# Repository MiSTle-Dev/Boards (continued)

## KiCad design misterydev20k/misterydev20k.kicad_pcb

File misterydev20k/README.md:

# MiSTeryDev20k

This is the first complete custom board which does *not* need daughter boards
like the [Tang Nano 20k](https://wiki.sipeed.com/hardware/en/tang/tang-nano-20k/nano-20k.html) or
the [Raspberry Pi Pico](https://www.raspberrypi.com/documentation/microcontrollers/pico-series.html).

The board features the [Gowin GW2AR-LV18QN88C8/I7](https://www.gowinsemi.com/en/product/detail/38/) FPGA present on the Tang Nano 20k and runs the same cores as that device including the [NanoMig](http://github.com/MiSTle-Dev/NanoMig) and [MisteryNano](http://github.com/MiSTle-Dev/MiSTeryNano).

This board can be manfactured through [JLCPCBs assembly service](http://jlcpcb.com) using the [production data](production).

The main objective of this board is to run known-good cores and
firmware and test a few features that couldn't be implemented and
tested with the Tang Nano 20k. These include:

  - Use the RP2040 for JTAG programming of the FPGA :heavy_check_mark:
    - Using openFPGAloader :heavy_check_mark:
    - Using Gowin Graphical Programmer :heavy_check_mark:
    - Using Gowin Programmer CLI :heavy_check_mark:
    - Extensive analysis and debugging of USB/JTAG commands as they pass the rp2040 :heavy_check_mark:
  - Additional access to the SD card directly from the RP2040 :heavy_check_mark:
    - SPI access is not possible since the SD card cannot return into SD card mode for FPGA usage
    - 1-bit SD mode work via software bitbang and achieves ~700kBytes/s :heavy_check_mark:
  - Control the FPGA directly from the RP2040 :heavy_check_mark:
    - Boot the FPGA from ```.fs``` file from SD card :heavy_check_mark:
    - Boot the FPGA from ```.bin``` file from SD card :heavy_check_mark:
  - Test SPI PSRAM
  - Optionally use the RP2040's native USB via the USB Hub

Further minor improvements over the existing boards are:

  - Two DB9 joysticks :heavy_check_mark: 
  - MIDI on M5 Stack connector :heavy_check_mark:

[Schematic PDF](misterydev20k_sch.pdf)
[Layout PDF](misterydev20k_board.pdf)	

## Current state

  - Schematic :heavy_check_mark:
  - Initial PCB layout :heavy_check_mark:
  - LCSC part mapping :heavy_check_mark:
  - BOM verification :heavy_check_mark:
  - Final PCB layout :heavy_check_mark:
  - Prepare JLCPCB [production data](production) :heavy_check_mark:
  - FPGA [stock](https://jlcpcb.com/partdetail/5794058-GW2AR_LV18QN88C8I7/C9900028472) :heavy_check_mark:
  - Order placed :heavy_check_mark:
  - Order shipped :heavy_check_mark:
  - Order stuck in customs :heavy_check_mark:	
  - Boards arrived :heavy_check_mark:
  - Basic 90% function test using Atari ST core :heavy_check_mark:
  - Extensive testing :heavy_check_mark:
  - New features :heavy_check_mark:

Upated in V1.1:
  - WS2812 was powered by 3.3V, corrected to 5V
  - JLCPCB BOM contained 16MBit flash for Pico and FPGA, are now 64MBit
  - Pico debug header labels on PCB were in reverse order

## Usage

The latest FPGA Companion has the ability to load cores
from SD card. Before doing so, please make sure you have a working
setup by placing the core and the ROMs in flash and using an SD card
with matching contents. Also build and install the latest FPGA
Companion for the DEV20K board to make sure the SD card and JTAG
functionality is included.

If this works fine, then replace the core in flash by any core that
does _not_ implement the FPGA Companions SPI interface.  You might use
this [test core](./test) which will display the MiSTle logo. Then
place the retro core you are using on the SD card. You can use the
```.fs``` file, but it's download from SD card to the FPGA will take
over 10 seconds as that's a huge ASCII file. Instead you might want
use the ```.bin``` file that is also generated by the
synthesis. Alternally, the ```.bin``` can be gerated from the
```.fs``` file using the gowin programmer:

```
programmer_cli --filestransform 1 --files test.fs
```

The core needs to be renamed to ```core.fs``` or ```core.bin``` when
placed on SD card. The board will then load the test core after
powerup. After 5 seconds it will timeout waiting for the core to
communicate. It will then search for ```core.bin``` and if that
fails for ```core.fs``` on the SD card. If present the core will
be downloaded to the FPGA and the system is rebooted using the
core.

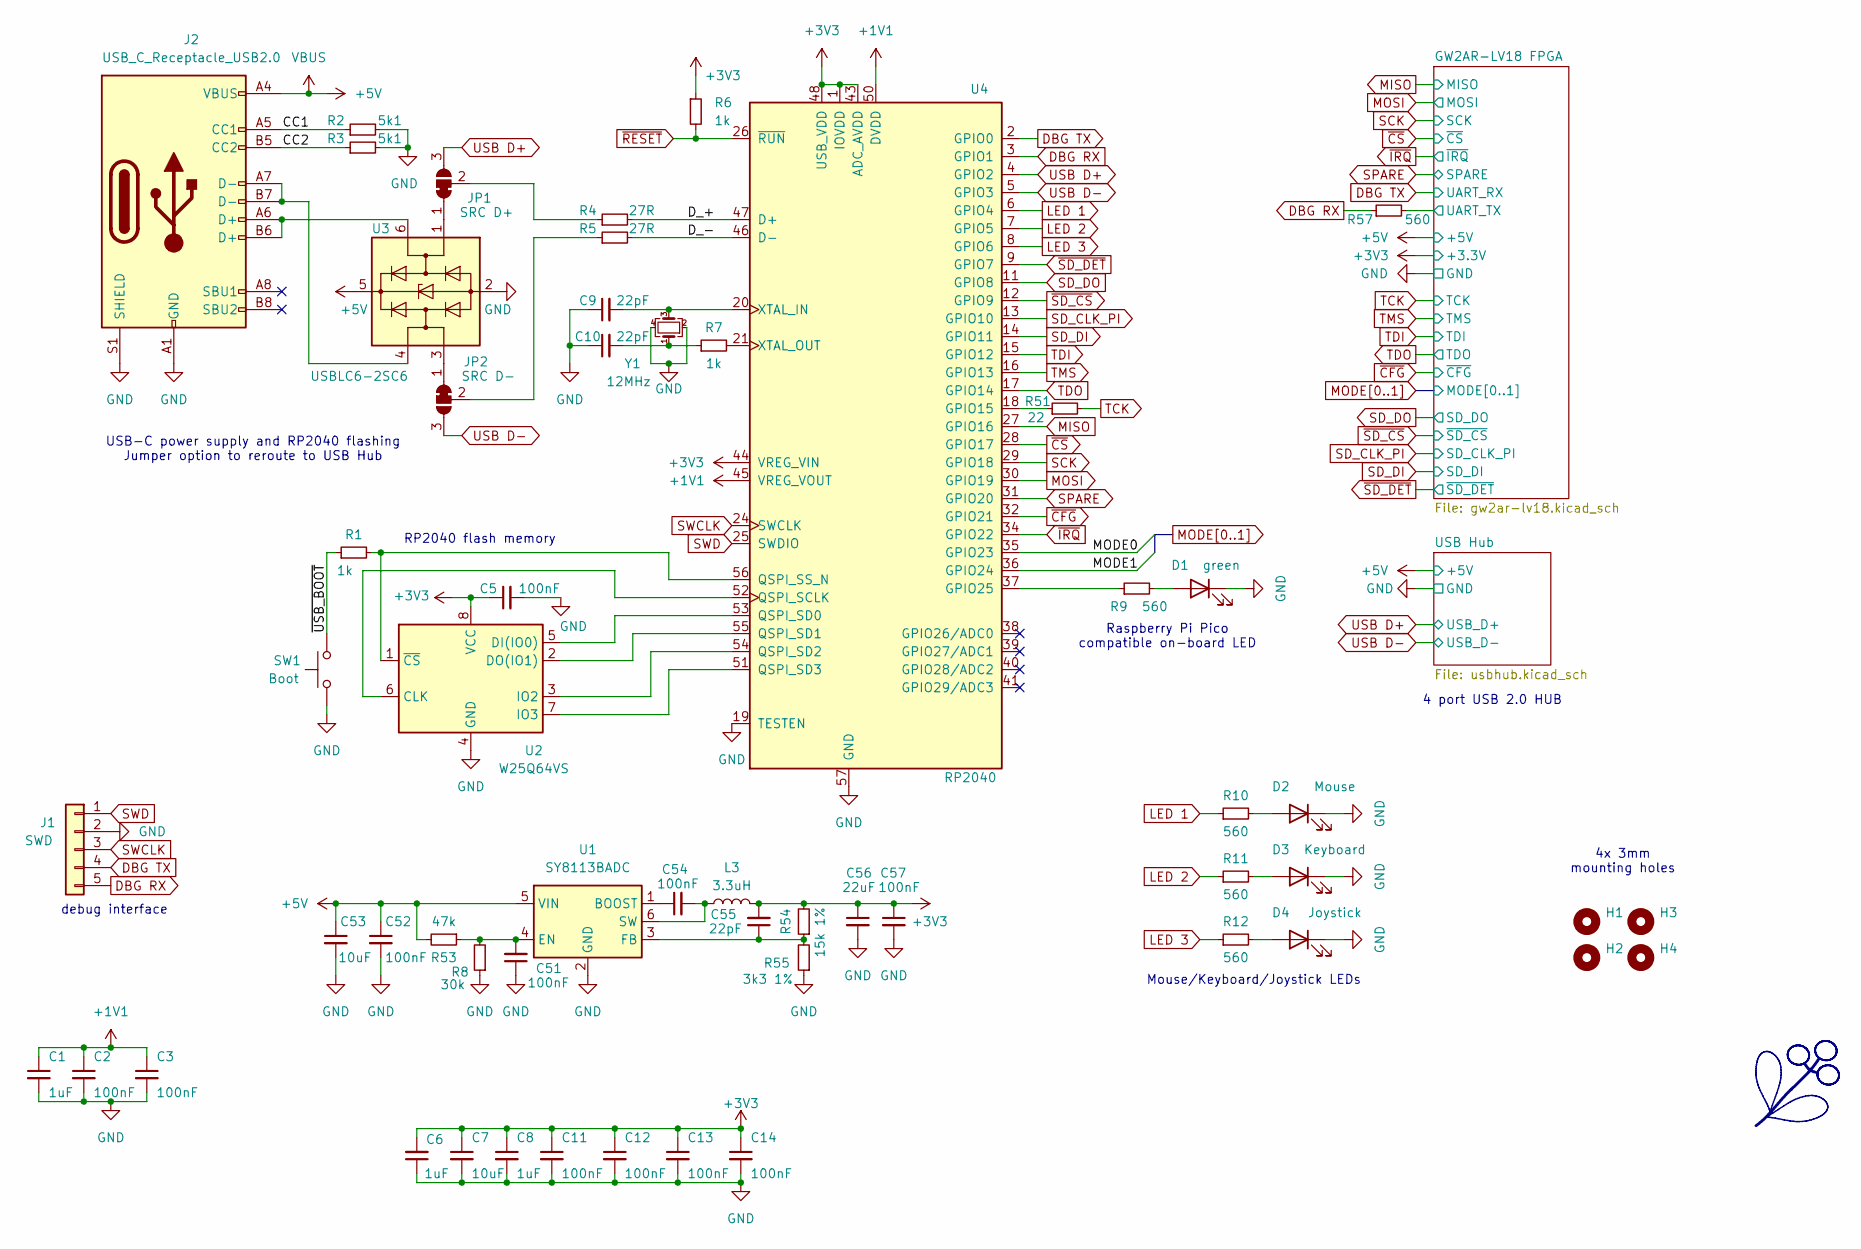
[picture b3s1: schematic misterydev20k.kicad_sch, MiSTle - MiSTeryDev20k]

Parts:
C1, C6, C8: 1uF; C_0402_1005Metric; LCSC Part # C52923
C2, C3, C5, C11, C12, C13, C14, C51, C54: 100nF; C_0402_1005Metric; LCSC Part # C1525
C7: 10uF; C_0402_1005Metric; LCSC Part # C15525
C9, C10, C55: 22pF; C_0402_1005Metric; LCSC Part # C1555
C52, C57: 100nF; C_0603_1608Metric; LCSC Part # C14663
C53: 10uF; C_0603_1608Metric; LCSC Part # C19702
C56: 22uF; C_0603_1608Metric; LCSC Part # C84419
D1: green; LED_0805_2012Metric; LCSC Part # C2297
D2: Mouse; LED_0805_2012Metric; LCSC Part # C2297
D3: Keyboard; LED_0805_2012Metric; LCSC Part # C2297
D4: Joystick; LED_0805_2012Metric; LCSC Part # C2297
H1, H2, H3, H4: MountingHole; MountingHole_3.2mm_M3
J1: SWD; PinHeader_1x05_P2.54mm_Vertical; LCSC Part # C492404
J2: USB_C_Receptacle_USB2.0; USB_C_Receptacle_HRO_TYPE-C-31-M-12; LCSC Part # C165948
JP1: SRC D+; SolderJumper-3_P1.3mm_Bridged12_RoundedPad1.0x1.5mm
JP2: SRC D-; SolderJumper-3_P1.3mm_Bridged12_RoundedPad1.0x1.5mm
L3: 3.3uH; L_Sunlord_MWSA0402S; LCSC Part # C408336
R1, R6, R7: 1k; R_0402_1005Metric; LCSC Part # C11702
R2, R3: 5k1; R_0402_1005Metric; LCSC Part # C25905
R4, R5: 27R; R_0603_1608Metric; LCSC Part # C25190
R8: 30k; R_0402_1005Metric; LCSC Part # C138008
R9, R10, R11, R12, R57: 560; R_0402_1005Metric; LCSC Part # C163460
R51: 22; R_0402_1005Metric; LCSC Part # C25092
R53: 47k; R_0402_1005Metric; LCSC Part # C11702
R54: 15k 1%; R_0402_1005Metric; LCSC Part # C25756
R55: 3k3 1%; R_0402_1005Metric; LCSC Part # C25890
SW1: Boot; SW_SPST_TL3342; LCSC Part # C318884
U1: SY8113BADC; TSOT-23-6; LCSC Part # C78989
U2: W25Q64VS; SOIC-8_5.23x5.23mm_P1.27mm; LCSC Part # C131025
U3: USBLC6-2SC6; SOT-23-6; LCSC Part # C2827654
U4: RP2040; RP2040-QFN-56; LCSC Part # C2040
Y1: 12MHz; Crystal_SMD_3225-4Pin_3.2x2.5mm; LCSC Part # C9002

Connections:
+1V1: C1.1, C2.1, C3.1, U4.23 (DVDD), U4.45 (VREG_VOUT), U4.50 (DVDD)
+3V3: C5.1, C6.2, C7.1, C8.1, C11.1, C12.1, C13.1, C14.1, C55.2, C56.1, C57.1, L3.2, R6.1, R54.2, U2.8 (VCC), U4.1 (IOVDD), U4.10 (IOVDD), U4.22 (IOVDD), U4.33 (IOVDD), U4.42 (IOVDD), U4.43 (ADC_AVDD), U4.44 (VREG_VIN), U4.48 (USB_VDD), U4.49 (IOVDD); also elsewhere on the board
+5V: C52.1, C53.1, J2.A4 (VBUS), J2.A9 (VBUS), J2.B4 (VBUS), J2.B9 (VBUS), R53.2, U1.5 (VIN), U3.5 (VBUS); also elsewhere on the board
/CC1: J2.A5 (CC1), R2.1
/CC2: J2.B5 (CC2), R3.1
/D_+: R4.2, U4.47 (D+)
/D_-: R5.2, U4.46 (D-)
/GW2AR-LV18 FPGA/UART_TX: R57.2; also elsewhere on the board
/~USB_BOOT: R1.1, SW1.2
DBG RX: J1.5, R57.1, U4.3 (GPIO1)
DBG TX: J1.4, U4.2 (GPIO0); also elsewhere on the board
GND: C1.2, C2.2, C3.2, C5.2, C6.1, C7.2, C8.2, C9.1, C10.1, C11.2, C12.2, C13.2, C14.2, C51.1, C52.2, C53.2, C56.2, C57.2, D1.1 (K), D2.1 (K), D3.1 (K), D4.1 (K), J1.2, J2.A1 (GND), J2.A12 (GND), J2.B1 (GND), J2.B12 (GND), J2.S1 (SHIELD), R2.2, R3.2, R8.1, R55.1, SW1.1, U1.2 (GND), U2.4 (GND), U3.2 (GND), U4.19 (TESTEN), U4.57 (GND), Y1.2, Y1.4; also elsewhere on the board
LED 1: R10.1, U4.6 (GPIO4)
LED 2: R11.1, U4.7 (GPIO5)
LED 3: R12.1, U4.8 (GPIO6)
MISO: U4.27 (GPIO16); also elsewhere on the board
MODE0: U4.35 (GPIO23); also elsewhere on the board
MODE1: U4.36 (GPIO24); also elsewhere on the board
MOSI: U4.30 (GPIO19); also elsewhere on the board
unnamed: C10.2, R7.1, Y1.1
unnamed: D1.2 (A), R9.2
unnamed: D2.2 (A), R10.2
unnamed: D3.2 (A), R11.2
unnamed: D4.2 (A), R12.2
unnamed: J2.A6 (D+), J2.B6 (D+), U3.6 (I/O1)
unnamed: J2.A7 (D-), J2.B7 (D-), U3.4 (I/O2)
unnamed: JP1.1 (A), U3.1 (I/O1)
unnamed: JP1.2 (C), R4.1
unnamed: JP2.1 (A), U3.3 (I/O2)
unnamed: JP2.2 (C), R5.1
unnamed: C54.1, U1.1 (BOOST)
unnamed: C51.2, R8.2, R53.1, U1.4 (EN)
unnamed: C55.1, R54.1, R55.2, U1.3 (FB)
unnamed: C54.2, L3.1, U1.6 (SW)
unnamed: U2.6 (CLK), U4.52 (QSPI_SCLK)
unnamed: U2.5 (DI(IO0)), U4.53 (QSPI_SD0)
unnamed: U2.2 (DO(IO1)), U4.55 (QSPI_SD1)
unnamed: U2.3 (IO2), U4.54 (QSPI_SD2)
unnamed: U2.7 (IO3), U4.51 (QSPI_SD3)
unnamed: R1.2, U2.1 (~CS), U4.56 (QSPI_SS_N)
unnamed: R51.1, U4.18 (GPIO15)
unnamed: R9.1, U4.37 (GPIO25)
unnamed: C9.2, U4.20 (XTAL_IN), Y1.3
unnamed: R7.2, U4.21 (XTAL_OUT)
SCK: U4.29 (GPIO18); also elsewhere on the board
SD_CLK_PI: U4.13 (GPIO10); also elsewhere on the board
SD_DI: U4.14 (GPIO11); also elsewhere on the board
SD_DO: U4.11 (GPIO8); also elsewhere on the board
SPARE: U4.31 (GPIO20); also elsewhere on the board
SWCLK: J1.3, U4.24 (SWCLK)
SWD: J1.1, U4.25 (SWDIO)
TCK: R51.2; also elsewhere on the board
TDI: U4.15 (GPIO12); also elsewhere on the board
TDO: U4.17 (GPIO14); also elsewhere on the board
TMS: U4.16 (GPIO13); also elsewhere on the board
USB D+: JP1.3 (B), U4.4 (GPIO2); also elsewhere on the board
USB D-: JP2.3 (B), U4.5 (GPIO3); also elsewhere on the board
~CFG: U4.32 (GPIO21); also elsewhere on the board
~CS: U4.28 (GPIO17); also elsewhere on the board
~IRQ: U4.34 (GPIO22); also elsewhere on the board
~RESET: R6.2, U4.26 (~RUN)
~SD_CS: U4.12 (GPIO9); also elsewhere on the board
~SD_DET: U4.9 (GPIO7); also elsewhere on the board

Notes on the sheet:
Mouse/Keyboard/Joystick LEDs
RP2040 flash memory
4x 3mm mounting holes
4 port USB 2.0 HUB
debug interface
Raspberry Pi Pico compatible on-board LED
USB-C power supply and RP2040 flashing Jumper option to reroute to USB Hub

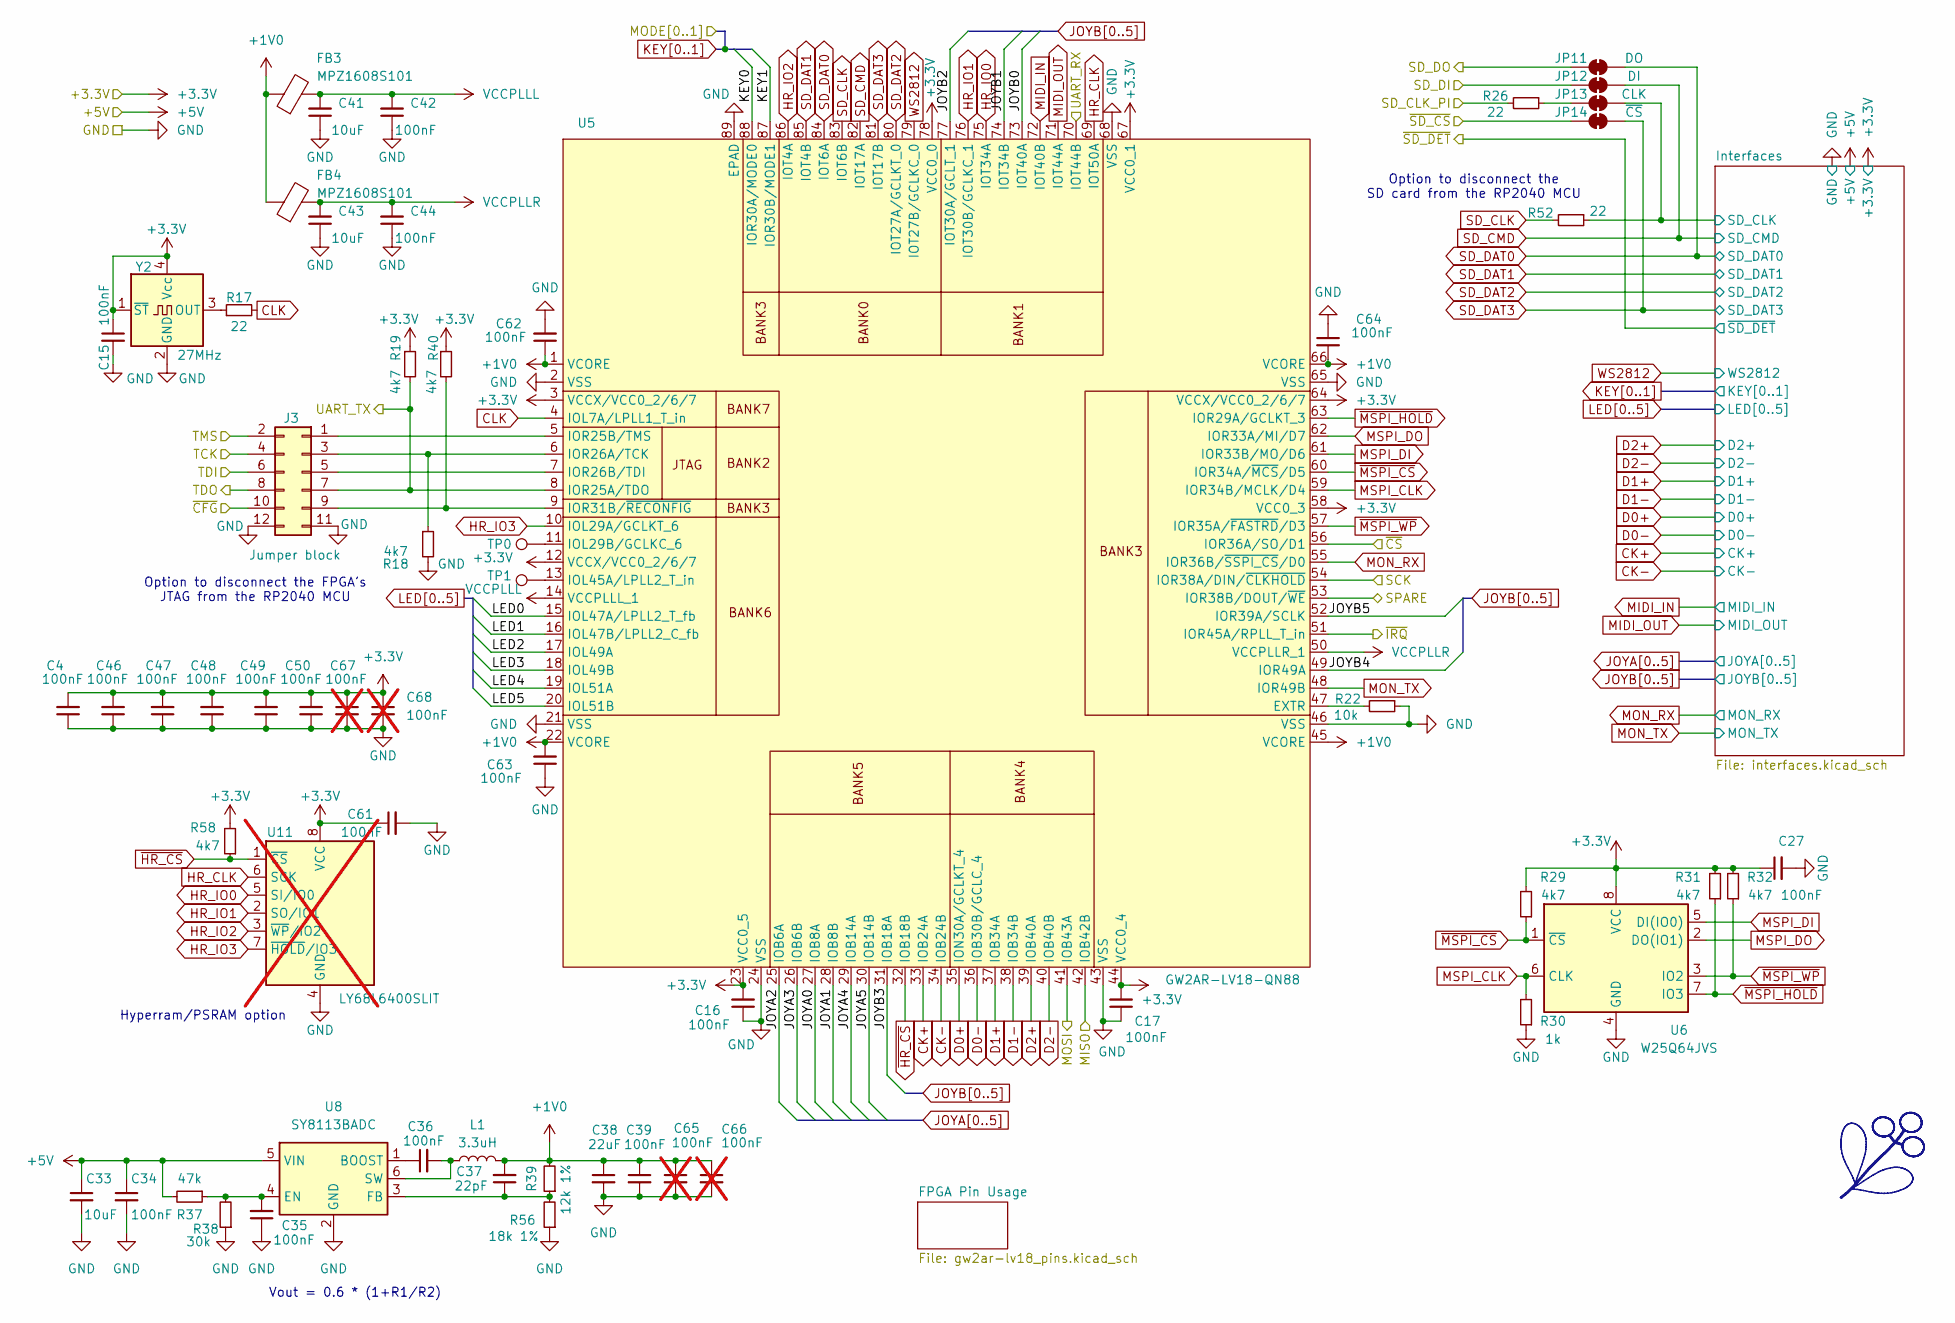
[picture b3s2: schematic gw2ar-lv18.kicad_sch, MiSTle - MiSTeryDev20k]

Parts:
C4, C15, C16, C17, C27, C35, C36, C42, C44, C46, C47, C48, C49, C50, C61, C62, C63, C64: 100nF; C_0402_1005Metric; LCSC Part # C1525
C33: 10uF; C_0603_1608Metric; LCSC Part # C19702
C34, C39: 100nF; C_0603_1608Metric; LCSC Part # C14663
C37: 22pF; C_0402_1005Metric; LCSC Part # C1555
C38: 22uF; C_0603_1608Metric; LCSC Part # C84419
C41, C43: 10uF; C_0402_1005Metric; LCSC Part # C15525
C65, C66, C67, C68: 100nF; C_0603_1608Metric; LCSC Part # C14663; not fitted
FB3, FB4: MPZ1608S101; L_0603_1608Metric; LCSC Part # C107332
J3: Jumper block; PinHeader_2x06_P2.54mm_Vertical; LCSC Part # C32713279
JP11: DO; SolderJumper-2_P1.3mm_Bridged_RoundedPad1.0x1.5mm
JP12: DI; SolderJumper-2_P1.3mm_Bridged_RoundedPad1.0x1.5mm
JP13: CLK; SolderJumper-2_P1.3mm_Bridged_RoundedPad1.0x1.5mm
JP14: ~{CS}; SolderJumper-2_P1.3mm_Bridged_RoundedPad1.0x1.5mm
L1: 3.3uH; L_Sunlord_MWSA0402S; LCSC Part # C408336
R17, R26, R52: 22; R_0402_1005Metric; LCSC Part # C25092
R18, R19, R29, R31, R32, R40, R58: 4k7; R_0402_1005Metric; LCSC Part # C25900
R22: 10k; R_0402_1005Metric; LCSC Part # C25744
R30: 1k; R_0402_1005Metric; LCSC Part # C11702
R37: 47k; R_0402_1005Metric; LCSC Part # C11702
R38: 30k; R_0402_1005Metric; LCSC Part # C138008
R39: 12k 1%; R_0402_1005Metric; LCSC Part # C25752
R56: 18k 1%; R_0402_1005Metric; LCSC Part # C138044
TP0, TP1: TestPoint; TestPoint_Pad_D1.0mm
U5: GW2AR-LV18-QN88; ArtInChip_QFN-88-1EP_10x10mm_P0.4mm_EP6.74x6.74mm_ThermalVi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; LCSC Part # C9900028472
U6: W25Q64JVS; SOIC-8_5.3x5.3mm_P1.27mm; LCSC Part # C179171
U8: SY8113BADC; TSOT-23-6; LCSC Part # C78989
U11: LY68L6400SLIT; SOIC-8_3.9x4.9mm_P1.27mm; LCSC Part # C261881; not fitted
Y2: 27MHz; Crystal_SMD_3225-4Pin_3.2x2.5mm; LCSC Part # C2901577

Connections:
+1V0: C37.2, C38.1, C39.1, C62.1, C63.2, C64.2, C65.1, C66.1, FB3.1, FB4.1, L1.2, R39.2, U5.1 (VCORE), U5.22 (VCORE), U5.45 (VCORE), U5.66 (VCORE)
+3V3: C4.2, C15.1, C16.2, C17.2, C27.1, C46.2, C47.2, C48.2, C49.2, C50.2, C61.1, C67.1, C68.1, R19.1, R29.2, R31.2, R32.2, R40.1, R58.2, U5.3 (VCCX/VCC0_2/6/7), U5.12 (VCCX/VCC0_2/6/7), U5.23 (VCC0_5), U5.44 (VCC0_4), U5.58 (VCC0_3), U5.64 (VCCX/VCC0_2/6/7), U5.67 (VCC0_1), U5.78 (VCC0_0), U6.8 (VCC), U11.8 (VCC), Y2.1 (~ST), Y2.4 (Vcc); also elsewhere on the board
+5V: C33.1, C34.1, R37.2, U8.5 (VIN); also elsewhere on the board
/GW2AR-LV18 FPGA/Interfaces/SD_CLK: JP13.2 (B), R52.1; also elsewhere on the board
/GW2AR-LV18 FPGA/UART_TX: J3.7, R19.2, U5.8 (IOR25A/TDO); also elsewhere on the board
CK+: U5.33 (IOB24A); also elsewhere on the board
CK-: U5.34 (IOB24B); also elsewhere on the board
CLK: R17.2, U5.4 (IOL7A/LPLL1_T_in)
D0+: U5.35 (ION30A/GCLKT_4); also elsewhere on the board
D0-: U5.36 (IOB30B/GCLC_4); also elsewhere on the board
D1+: U5.37 (IOB34A); also elsewhere on the board
D1-: U5.38 (IOB34B); also elsewhere on the board
D2+: U5.39 (IOB40A); also elsewhere on the board
D2-: U5.40 (IOB40B); also elsewhere on the board
DBG TX: U5.70 (IOT44B); also elsewhere on the board
GND: C4.1, C15.2, C16.1, C17.1, C27.2, C33.2, C34.2, C35.1, C38.2, C39.2, C41.1, C42.1, C43.1, C44.1, C46.1, C47.1, C48.1, C49.1, C50.1, C61.2, C62.2, C63.1, C64.1, C65.2, C66.2, C67.2, C68.2, J3.11, J3.12, R18.2, R22.1, R30.1, R38.1, R56.1, U5.2 (VSS), U5.21 (VSS), U5.24 (VSS), U5.43 (VSS), U5.46 (VSS), U5.65 (VSS), U5.68 (VSS), U5.89 (EPAD), U6.4 (GND), U8.2 (GND), U11.4 (GND), Y2.2 (GND); also elsewhere on the board
HR_CLK: U5.69 (IOT50A), U11.6 (SCK)
HR_IO0: U5.75 (IOT34A), U11.5 (SI/IO0)
HR_IO1: U5.76 (IOT30B/GCLKC_1), U11.2 (SO/IO1)
HR_IO2: U5.86 (IOT4A), U11.3 (~WP/IO2)
HR_IO3: U5.10 (IOL29A/GCLKT_6), U11.7 (~HOLD/IO3)
JOYA0: U5.27 (IOB8A); also elsewhere on the board
JOYA1: U5.28 (IOB8B); also elsewhere on the board
JOYA2: U5.25 (IOB6A); also elsewhere on the board
JOYA3: U5.26 (IOB6B); also elsewhere on the board
JOYA4: U5.29 (IOB14A); also elsewhere on the board
JOYA5: U5.30 (IOB14B); also elsewhere on the board
JOYB0: U5.73 (IOT40A); also elsewhere on the board
JOYB1: U5.74 (IOT34B); also elsewhere on the board
JOYB2: U5.77 (IOT30A/GCLT_1); also elsewhere on the board
JOYB3: U5.31 (IOB18A); also elsewhere on the board
JOYB4: U5.49 (IOR49A); also elsewhere on the board
JOYB5: U5.52 (IOR39A/SCLK); also elsewhere on the board
LED0: U5.15 (IOL47A/LPLL2_T_fb); also elsewhere on the board
LED1: U5.16 (IOL47B/LPLL2_C_fb); also elsewhere on the board
LED2: U5.17 (IOL49A); also elsewhere on the board
LED3: U5.18 (IOL49B); also elsewhere on the board
LED4: U5.19 (IOL51A); also elsewhere on the board
LED5: U5.20 (IOL51B); also elsewhere on the board
MIDI_IN: U5.72 (IOT40B); also elsewhere on the board
MIDI_OUT: U5.71 (IOT44A); also elsewhere on the board
MISO: U5.42 (IOB42B); also elsewhere on the board
MODE0: U5.88 (IOR30A/MODE0); also elsewhere on the board
MODE1: U5.87 (IOR30B/MODE1); also elsewhere on the board
MON_RX: U5.55 (IOR36B/~SSPI_CS/D0); also elsewhere on the board
MON_TX: U5.48 (IOR49B); also elsewhere on the board
MOSI: U5.41 (IOB43A); also elsewhere on the board
MSPI_CLK: R30.2, U5.59 (IOR34B/MCLK/D4), U6.6 (CLK)
MSPI_DI: U5.61 (IOR33B/MO/D6), U6.5 (DI(IO0))
MSPI_DO: U5.62 (IOR33A/MI/D7), U6.2 (DO(IO1))
unnamed: J3.1, U5.5 (IOR25B/TMS)
unnamed: J3.3, R18.1, U5.6 (IOR26A/TCK)
unnamed: J3.5, U5.7 (IOR26B/TDI)
unnamed: J3.9, R40.2, U5.9 (IOR31B/~RECONFIG)
unnamed: JP13.1 (A), R26.1
unnamed: R22.2, U5.47 (EXTR)
unnamed: TP0.1 (1_1), U5.11 (IOL29B/GCLKC_6)
unnamed: TP1.1 (1_1), U5.13 (IOL45A/LPLL2_T_in)
unnamed: C36.1, U8.1 (BOOST)
unnamed: C35.2, R37.1, R38.2, U8.4 (EN)
unnamed: C37.1, R39.1, R56.2, U8.3 (FB)
unnamed: C36.2, L1.1, U8.6 (SW)
unnamed: R17.1, Y2.3 (OUT)
SCK: U5.54 (IOR38A/DIN/~CLKHOLD); also elsewhere on the board
SD_CLK: R52.2, U5.83 (IOT6B)
SD_CLK_PI: R26.2; also elsewhere on the board
SD_CMD: JP12.2 (B), U5.82 (IOT17A); also elsewhere on the board
SD_DAT0: JP11.2 (B), U5.84 (IOT6A); also elsewhere on the board
SD_DAT1: U5.85 (IOT4B); also elsewhere on the board
SD_DAT2: U5.80 (IOT27A/GCLKT_0); also elsewhere on the board
SD_DAT3: JP14.2 (B), U5.81 (IOT17B); also elsewhere on the board
SD_DI: JP12.1 (A); also elsewhere on the board
SD_DO: JP11.1 (A); also elsewhere on the board
SPARE: U5.53 (IOR38B/DOUT/~WE); also elsewhere on the board
TCK: J3.4; also elsewhere on the board
TDI: J3.6; also elsewhere on the board
TDO: J3.8; also elsewhere on the board
TMS: J3.2; also elsewhere on the board
VCCPLLL: C41.2, C42.2, FB3.2, U5.14 (VCCPLLL_1)
VCCPLLR: C43.2, C44.2, FB4.2, U5.50 (VCCPLLR_1)
WS2812: U5.79 (IOT27B/GCLKC_0); also elsewhere on the board
~CFG: J3.10; also elsewhere on the board
~CS: U5.56 (IOR36A/SO/D1); also elsewhere on the board
~HR_CS: R58.1, U5.32 (IOB18B), U11.1 (~CS)
~IRQ: U5.51 (IOR45A/RPLL_T_in); also elsewhere on the board
~MSPI_CS: R29.1, U5.60 (IOR34A/~MCS/D5), U6.1 (~CS)
~MSPI_HOLD: R31.1, U5.63 (IOR29A/GCLKT_3), U6.7 (IO3)
~MSPI_WP: R32.1, U5.57 (IOR35A/~FASTRD/D3), U6.3 (IO2)
~SD_CS: JP14.1 (A); also elsewhere on the board

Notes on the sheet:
Option to disconnect the SD card from the RP2040 MCU
Vout = 0.6 * (1+R1/R2)
Hyperram/PSRAM option
Option to disconnect the FPGA's JTAG from the RP2040 MCU

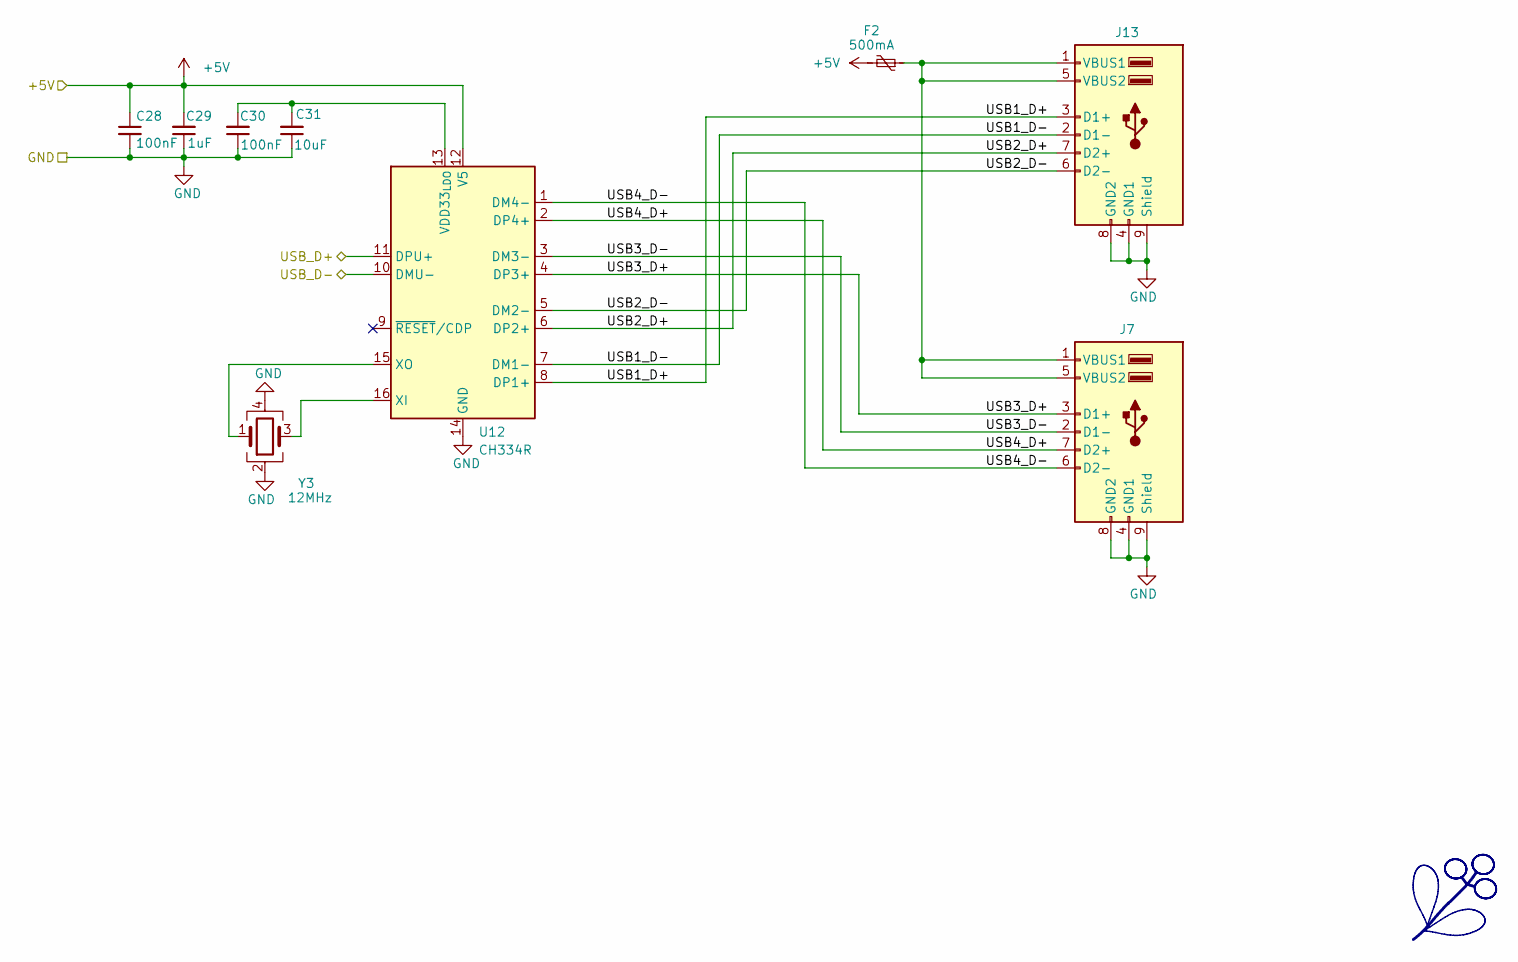
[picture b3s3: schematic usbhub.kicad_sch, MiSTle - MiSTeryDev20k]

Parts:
C28, C30: 100nF; C_0402_1005Metric; LCSC Part # C1525
C29: 1uF; C_0402_1005Metric; LCSC Part # C52923
C31: 10uF; C_0402_1005Metric; LCSC Part # C15525
F2: 500mA; Fuse_1206_3216Metric; LCSC Part # C70076
J7, J13: USB_A_Stacked; USB_A_Wuerth_61400826021_Horizontal_Stacked; LCSC Part # C456021
U12: CH334R; QSOP-16_3.9x4.9mm_P0.635mm; LCSC Part # C4154405
Y3: 12MHz; Crystal_SMD_3225-4Pin_3.2x2.5mm; LCSC Part # C9002

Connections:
+5V: C28.1, C29.2, F2.2, U12.12 (V5); also elsewhere on the board
/USB Hub/USB1_D+: J13.3 (D1+), U12.8 (DP1+)
/USB Hub/USB1_D-: J13.2 (D1-), U12.7 (DM1-)
/USB Hub/USB2_D+: J13.7 (D2+), U12.6 (DP2+)
/USB Hub/USB2_D-: J13.6 (D2-), U12.5 (DM2-)
/USB Hub/USB3_D+: J7.3 (D1+), U12.4 (DP3+)
/USB Hub/USB3_D-: J7.2 (D1-), U12.3 (DM3-)
/USB Hub/USB4_D+: J7.7 (D2+), U12.2 (DP4+)
/USB Hub/USB4_D-: J7.6 (D2-), U12.1 (DM4-)
GND: C28.2, C29.1, C30.1, C31.1, J7.4 (GND1), J7.8 (GND2), J7.9 (Shield), J13.4 (GND1), J13.8 (GND2), J13.9 (Shield), U12.14 (GND), Y3.2, Y3.4; also elsewhere on the board
unnamed: F2.1, J7.1 (VBUS1), J7.5 (VBUS2), J13.1 (VBUS1), J13.5 (VBUS2)
unnamed: C30.2, C31.2, U12.13 (VDD33_{LDO})
unnamed: U12.16 (XI), Y3.3
unnamed: U12.15 (XO), Y3.1
USB D+: U12.11 (DPU+); also elsewhere on the board
USB D-: U12.10 (DMU-); also elsewhere on the board

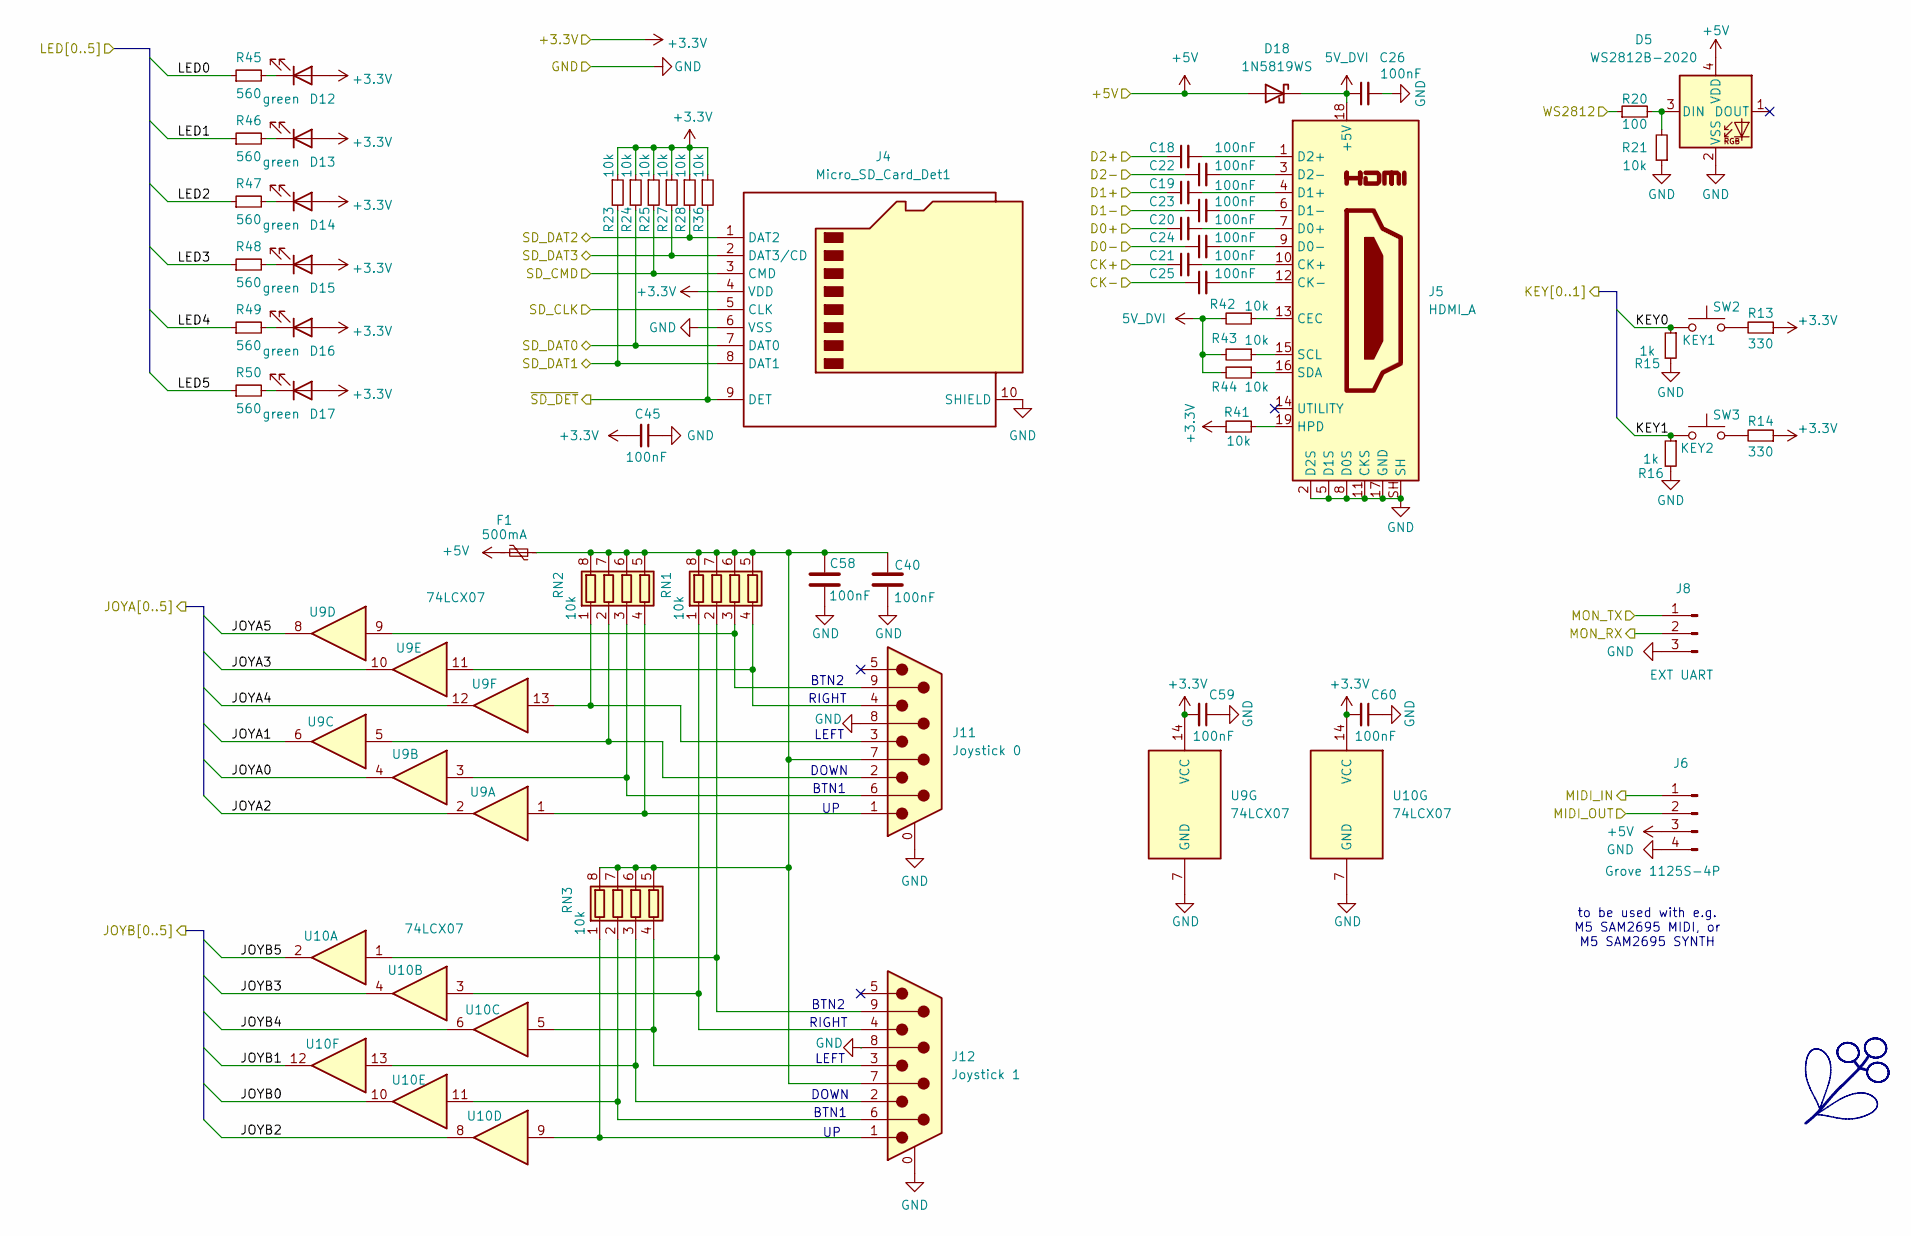
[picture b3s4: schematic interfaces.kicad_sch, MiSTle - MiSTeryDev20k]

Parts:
C18, C19, C20, C21, C22, C23, C24, C25, C26, C40, C45, C58, C59, C60: 100nF; C_0402_1005Metric; LCSC Part # C1525
D5: WS2812B-2020; LED_WS2812B-2020_PLCC4_2.0x2.0mm; LCSC Part # C965555
D12, D13, D14, D15, D16, D17: green; LED_0805_2012Metric; LCSC Part # C2297
D18: 1N5819WS; D_SOD-323; LCSC Part # C191023
F1: 500mA; Fuse_1206_3216Metric; LCSC Part # C70076
J4: Micro_SD_Card_Det1; TF-015; LCSC Part # C393941
J5: HDMI_A; HDMI_A_Molex_208658-1001_Horizontal; LCSC Part # C720616
J6: Grove 1125S-4P; NS-Tech_Grove_1x04_P2mm_Vertical
J8: EXT UART; PinHeader_1x03_P2.54mm_Vertical
J11: Joystick 0; DSUB-9_Pins_Horizontal_P2.77x2.84mm_EdgePinOffset7.70mm_Hou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; LCSC Part # C141880
J12: Joystick 1; DSUB-9_Pins_Horizontal_P2.77x2.84mm_EdgePinOffset7.70mm_Hou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; LCSC Part # C141880
R13, R14: 330; R_0402_1005Metric; LCSC Part # C105875
R15, R16: 1k; R_0402_1005Metric; LCSC Part # C11702
R20: 100; R_0402_1005Metric; LCSC Part # C25076
R21, R23, R24, R25, R27, R28, R36, R41, R42, R43, R44: 10k; R_0402_1005Metric; LCSC Part # C25744
R45, R46, R47, R48, R49, R50: 560; R_0402_1005Metric; LCSC Part # C163460
RN1, RN2, RN3: 10k; R_Array_Concave_4x0603; LCSC Part # C110924
SW2: KEY1; SW_SPST_TL3342; LCSC Part # C318884
SW3: KEY2; SW_SPST_TL3342; LCSC Part # C318884
U9, U10: 74LCX07; TSSOP-14_4.4x5mm_P0.65mm; LCSC Part # C2676034

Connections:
5V_DVI: C26.1, D18.1 (K), J5.18 (+5V), R42.2, R43.2, R44.2
+3V3: C45.2, C59.2, C60.2, D12.2 (A), D13.2 (A), D14.2 (A), D15.2 (A), D16.2 (A), D17.2 (A), J4.4 (VDD), R13.1, R14.1, R23.1, R24.1, R25.1, R27.1, R28.1, R36.1, R41.1, U9.14 (VCC), U10.14 (VCC); also elsewhere on the board
+5V: D5.4 (VDD), D18.2 (A), F1.2, J6.3; also elsewhere on the board
/GW2AR-LV18 FPGA/Interfaces/SD_CLK: J4.5 (CLK); also elsewhere on the board
CK+: C21.1; also elsewhere on the board
CK-: C25.1; also elsewhere on the board
D0+: C20.1; also elsewhere on the board
D0-: C24.1; also elsewhere on the board
D1+: C19.1; also elsewhere on the board
D1-: C23.1; also elsewhere on the board
D2+: C18.1; also elsewhere on the board
D2-: C22.1; also elsewhere on the board
GND: C26.2, C40.1, C45.1, C58.1, C59.1, C60.1, D5.2 (VSS), J4.6 (VSS), J4.10 (SHIELD), J5.2 (D2S), J5.5 (D1S), J5.8 (D0S), J5.11 (CKS), J5.17 (GND), J5.SH, J6.4, J8.3, J11.0 (PAD), J11.8, J12.0 (PAD), J12.8, R15.2, R16.2, R21.1, U9.7 (GND), U10.7 (GND); also elsewhere on the board
JOYA0: U9.4; also elsewhere on the board
JOYA1: U9.6; also elsewhere on the board
JOYA2: U9.2; also elsewhere on the board
JOYA3: U9.10; also elsewhere on the board
JOYA4: U9.12; also elsewhere on the board
JOYA5: U9.8; also elsewhere on the board
JOYB0: U10.10; also elsewhere on the board
JOYB1: U10.12; also elsewhere on the board
JOYB2: U10.8; also elsewhere on the board
JOYB3: U10.4; also elsewhere on the board
JOYB4: U10.6; also elsewhere on the board
JOYB5: U10.2; also elsewhere on the board
LED0: R45.1; also elsewhere on the board
LED1: R46.1; also elsewhere on the board
LED2: R47.1; also elsewhere on the board
LED3: R48.1; also elsewhere on the board
LED4: R49.1; also elsewhere on the board
LED5: R50.1; also elsewhere on the board
MIDI_IN: J6.1; also elsewhere on the board
MIDI_OUT: J6.2; also elsewhere on the board
MODE0: R15.1, SW2.2; also elsewhere on the board
MODE1: R16.1, SW3.2; also elsewhere on the board
MON_RX: J8.2; also elsewhere on the board
MON_TX: J8.1; also elsewhere on the board
unnamed: D5.3 (DIN), R20.2, R21.2
unnamed: D12.1 (K), R45.2
unnamed: D13.1 (K), R46.2
unnamed: D14.1 (K), R47.2
unnamed: D15.1 (K), R48.2
unnamed: D16.1 (K), R49.2
unnamed: D17.1 (K), R50.2
unnamed: J5.13 (CEC), R42.1
unnamed: C21.2, J5.10 (CK+)
unnamed: C25.2, J5.12 (CK-)
unnamed: C20.2, J5.7 (D0+)
unnamed: C24.2, J5.9 (D0-)
unnamed: C19.2, J5.4 (D1+)
unnamed: C23.2, J5.6 (D1-)
unnamed: C18.2, J5.1 (D2+)
unnamed: C22.2, J5.3 (D2-)
unnamed: J5.19 (HPD), R41.2
unnamed: J5.15 (SCL), R43.1
unnamed: J5.16 (SDA), R44.1
unnamed: R13.2, SW2.1
unnamed: R14.2, SW3.1
unnamed: J12.4, RN1.1 (R1.1), U10.3
unnamed: C40.2, C58.2, F1.1, J11.7, J12.7, RN1.5 (R4.2), RN1.6 (R3.2), RN1.7 (R2.2), RN1.8 (R1.2), RN2.5 (R4.2), RN2.6 (R3.2), RN2.7 (R2.2), RN2.8 (R1.2), RN3.5 (R4.2), RN3.6 (R3.2), RN3.7 (R2.2), RN3.8 (R1.2)
unnamed: J12.9, RN1.2 (R2.1), U10.1
unnamed: J11.9, RN1.3 (R3.1), U9.9
unnamed: J11.4, RN1.4 (R4.1), U9.11
unnamed: J11.3, RN2.1 (R1.1), U9.13
unnamed: J11.2, RN2.2 (R2.1), U9.5
unnamed: J11.6, RN2.3 (R3.1), U9.3
unnamed: J11.1, RN2.4 (R4.1), U9.1
unnamed: J12.1, RN3.1 (R1.1), U10.9
unnamed: J12.6, RN3.2 (R2.1), U10.11
unnamed: J12.2, RN3.3 (R3.1), U10.13
unnamed: J12.3, RN3.4 (R4.1), U10.5
SD_CMD: J4.3 (CMD), R25.2; also elsewhere on the board
SD_DAT0: J4.7 (DAT0), R24.2; also elsewhere on the board
SD_DAT1: J4.8 (DAT1), R23.2; also elsewhere on the board
SD_DAT2: J4.1 (DAT2), R28.2; also elsewhere on the board
SD_DAT3: J4.2 (DAT3/CD), R27.2; also elsewhere on the board
WS2812: R20.1; also elsewhere on the board
~SD_DET: J4.9 (DET), R36.2; also elsewhere on the board

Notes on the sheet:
LEFT
BTN1
BTN2
RIGHT
DOWN
to be used with e.g. M5 SAM2695 MIDI, or M5 SAM2695 SYNTH
